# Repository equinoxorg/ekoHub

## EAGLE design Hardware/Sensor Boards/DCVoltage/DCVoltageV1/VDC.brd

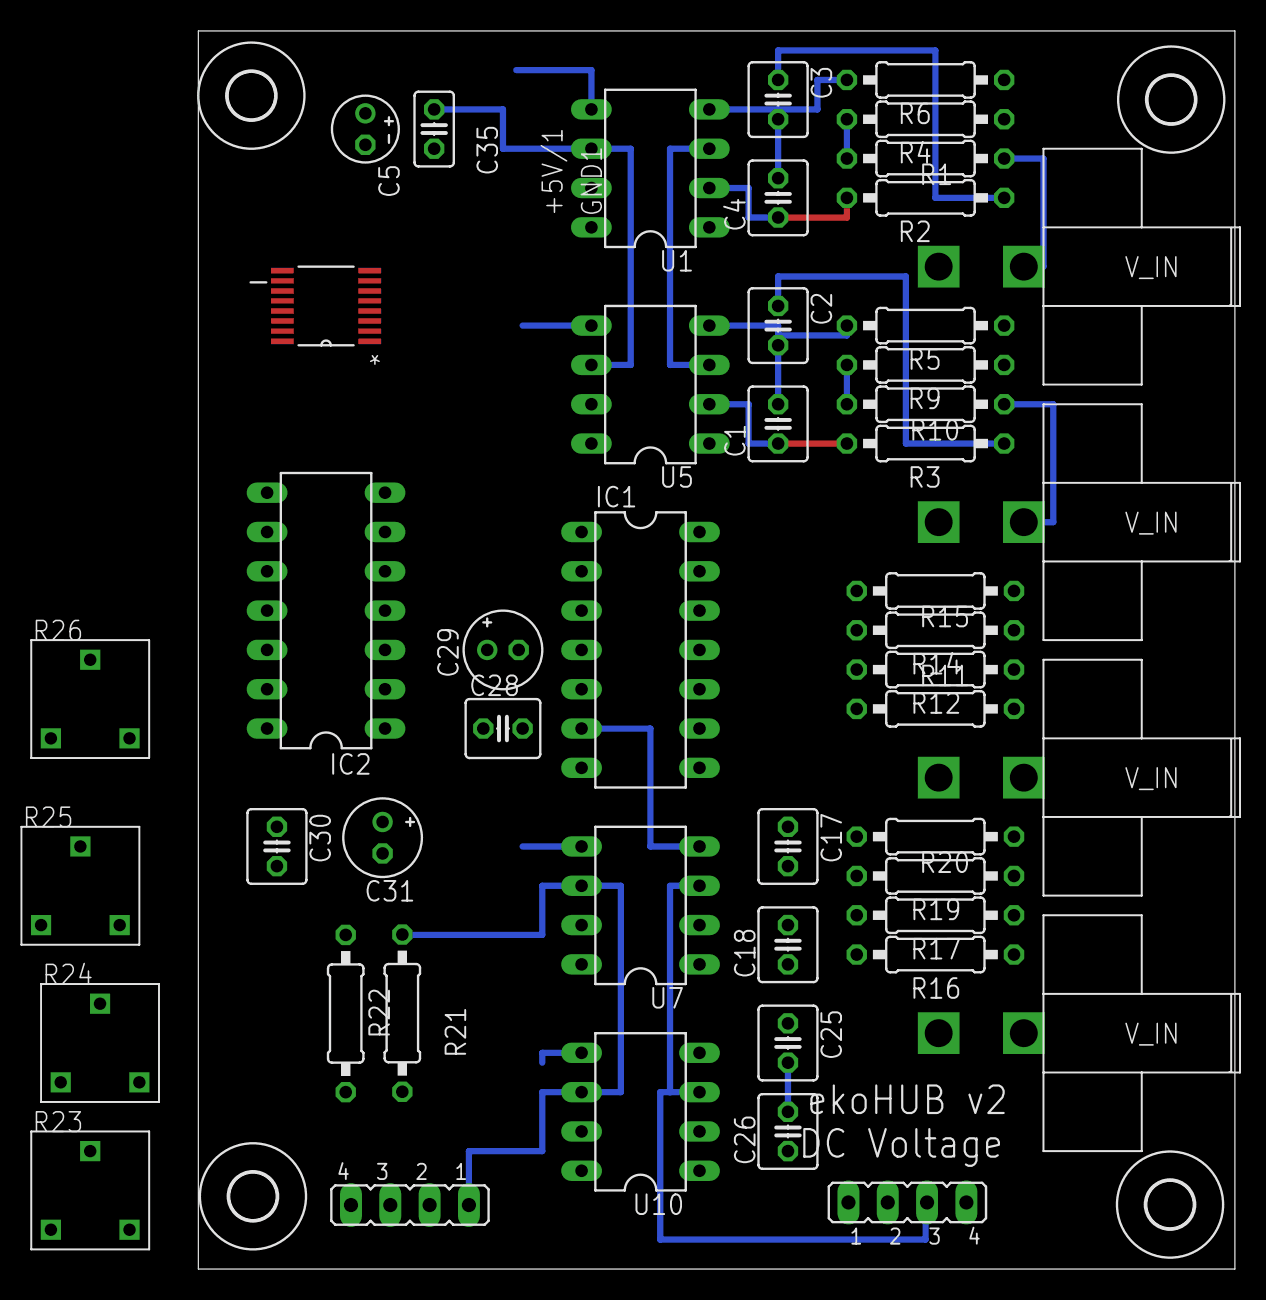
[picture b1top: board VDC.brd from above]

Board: 2 copper layers, 67.0 x 80.0 mm, 53 parts (0 on the bottom side), 34 nets.

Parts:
C1, C2, C3, C4, C17, C18, C25, C26, C28, C30: C025-040X050
C5: E2-4
C29, C31: E2-5
C35: C025-025X050
IC1, IC2: MCP604P; DIL14
JP1, JP3: JP4
R1, R2, R3, R4, R5, R6, R9, R10, R11, R12, R14, R15, R16, R17, R19, R20, R21, R22: 0207/10
R23, R24, R25, R26: IRG2014TRIM
U1, U5, U7, U10: IL300; DIL08
U13: AD7993BRUZ-0; SOP65P640X120-16N
U$1, U$2, U$3, U$4: 3,0
U$5, U$6, U$7, U$8: INPUT_VOLTAGE_CONNECTOR

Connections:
+5V/1: C28.1, C29.+, IC1.4, JP3.3, U1.3, U5.3, U7.3, U10.3
+5V/2: C5.+, C30.1, C31.+, C35.1, IC2.4, JP1.1, R21.1, R22.1, U1.6, U5.6, U7.6, U10.6, U13.5, U13.6
DC_OUT1: IC2.1, IC2.2, U13.7
DC_OUT2: IC2.6, IC2.7, U13.10
DC_OUT3: IC2.8, IC2.9, U13.8
DC_OUT4: IC2.13, IC2.14, U13.9
DC_SENSE1: R1.2, U$8.V+
DC_SENSE2: R10.2, U$7.V+
DC_SENSE3: R15.2, U$6.V+
DC_SENSE4: R20.2, U$5.V+
GND1: C28.2, C29.-, IC1.11, IC1.13, JP3.4, R4.1, R5.1, R6.1, R9.1, R12.1, R14.1, R17.1, R19.1, U1.1, U5.1, U7.1, U10.1, U$5.V-, U$6.V-, U$7.V-, U$8.V-
GND2: C5.-, C30.2, C31.-, C35.2, IC2.11, JP1.2, R23.P$1, R23.P$2, R24.P$1, R24.P$2, R25.P$1, R25.P$2, R26.P$1, R26.P$2, U13.1, U13.2, U13.3, U13.4, U13.11, U13.16
unnamed: C3.2, C4.2, R6.2, U1.4
unnamed: C1.2, C2.2, IC1.9, R5.2, U5.4
unnamed: IC2.12, R26.P$3, U1.5
unnamed: C4.1, R2.2, U1.2
unnamed: C3.1, IC1.14, R2.1
unnamed: C1.1, R3.2, U5.2
unnamed: C2.1, IC1.8, R3.1
unnamed: IC1.12, R1.1, R4.2
unnamed: IC2.10, R25.P$3, U5.5
unnamed: IC1.10, R9.2, R10.1
unnamed: C18.1, R11.2, U7.2
unnamed: C17.1, IC1.7, R11.1
unnamed: IC2.5, R24.P$3, U7.5
unnamed: IC1.5, R14.2, R15.1
unnamed: C25.2, C26.2, IC1.2, R17.2, U10.4
unnamed: C26.1, R16.2, U10.2
unnamed: C25.1, IC1.1, R16.1
unnamed: IC2.3, R23.P$3, U10.5
unnamed: IC1.3, R19.2, R20.1
unnamed: C17.2, C18.2, IC1.6, R12.2, U7.4
SCL: JP1.4, R22.2, U13.15
SDA: JP1.3, R21.2, U13.14

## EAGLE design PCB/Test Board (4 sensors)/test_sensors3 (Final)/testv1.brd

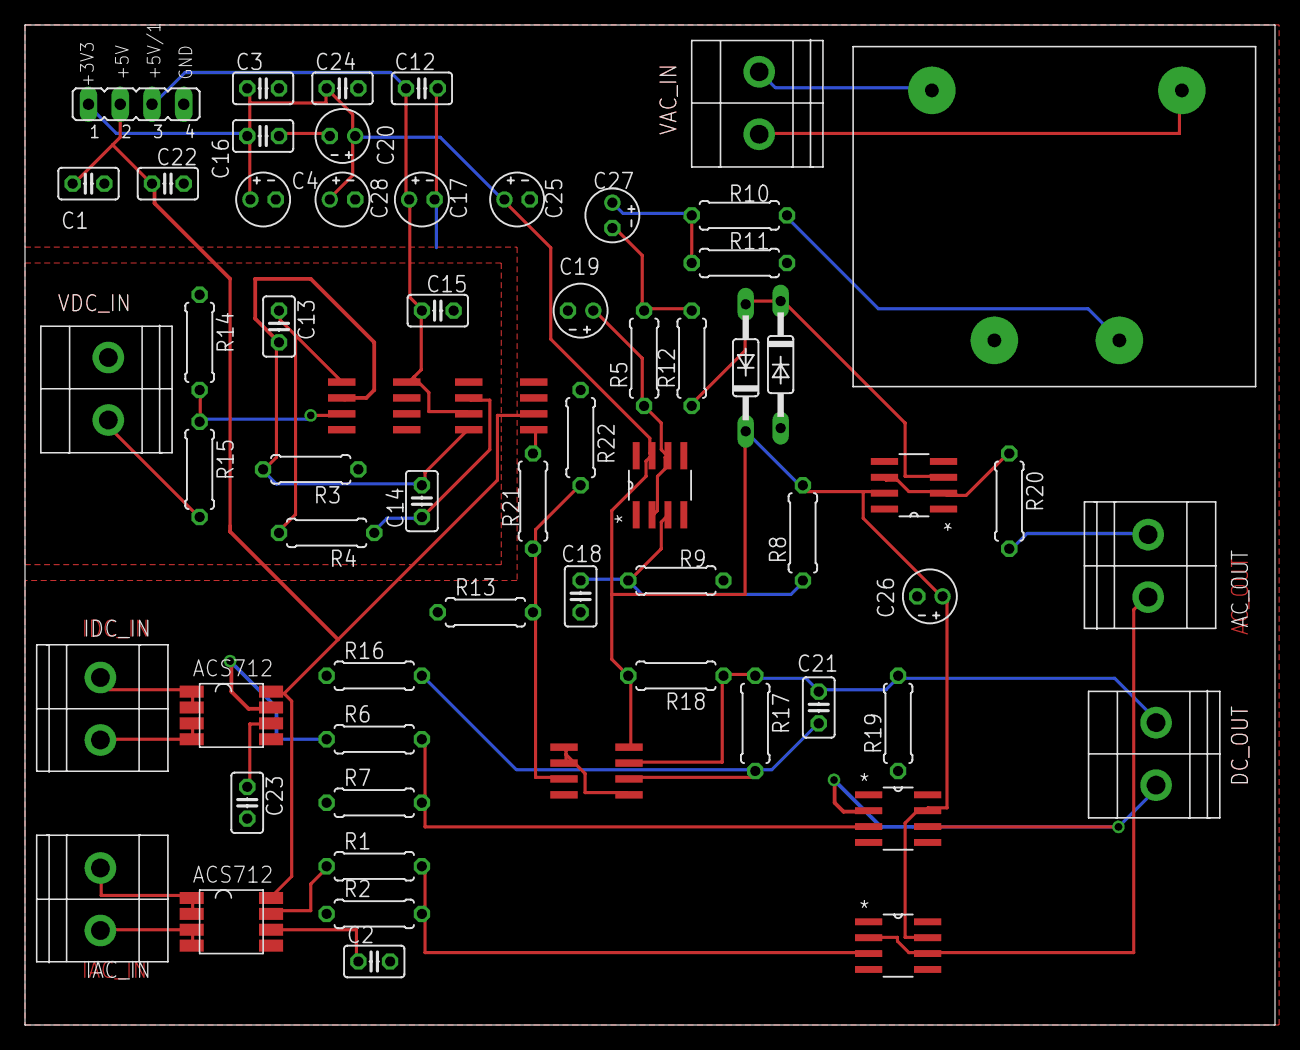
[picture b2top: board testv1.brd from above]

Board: 2 copper layers, 100.0 x 80.0 mm, 62 parts (0 on the bottom side), 38 nets.

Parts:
AC_OUT: CTB1500/2; CTB1500-2
C1, C2, C3, C12, C13, C14, C15, C16, C18, C21, C22, C23, C24: C025-025X050
C4, C17, C19, C20, C25, C26, C27, C28: E2-4
DC_OUT: CTB1500/2; CTB1500-2
IAC_IN: CTB1500/2; CTB1500-2
IC1, IC2: MCP602SN; SO08
IDC_IN: CTB1500/2; CTB1500-2
JP1: JP4
R1, R2, R3, R4, R5, R6, R7, R8, R9, R10, R11, R12, R13, R14, R15, R16, R17, R18, R19, R20, R21, R22: 0207/7
U2, U4, U5, U6: MCP601-E/SN; SOIC127P600X175-8N
U3: IL300; SO8
U$1, U$10: ACS712; SOIC8
U$6: 4408
U$7, U$8: SD103A; D035-10
VAC_IN: CTB1500/2; CTB1500-2
VDC_IN: CTB1500/2; CTB1500-2

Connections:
+3V3: C3.1, C4.+, C16.1, C20.+, C24.1, C25.+, C26.+, C28.+, IC2.8, JP1.1, R8.2, R18.2, U2.7, U4.7, U5.7, U6.7, U$7.C
+5V: C1.1, C22.1, JP1.2, U3.6, U$1.8, U$10.8
+5V/1: C12.1, C15.1, C17.+, IC1.8, JP1.3, U3.3
DC_SENSE: R15.2, VDC_IN.P$2
GND: C1.2, C2.2, C3.2, C4.-, C18.2, C19.-, C22.2, C23.2, C24.2, C25.-, C26.-, C28.-, IC2.4, JP1.4, R2.1, R7.1, R9.1, R11.1, R13.1, R16.1, R19.1, R22.1, U2.4, U4.4, U5.4, U6.4, U$1.5, U$6.PIN9, U$8.A, U$10.5
GND1: C12.2, C15.2, C17.-, IC1.4, IC1.5, IC1.6, R3.1, R14.1, U3.1, VDC_IN.P$1
GND2: C16.2, C20.-
IAC_OUT: AC_OUT.P$1, U2.2, U2.6
IDC_OUT: DC_OUT.P$2, U4.2, U4.6
unnamed: IAC_IN.P$2, U$1.1, U$1.2
unnamed: IAC_IN.P$1, U$1.3, U$1.4
unnamed: R1.1, U$1.7
unnamed: C2.1, U$1.6
unnamed: C13.2, C14.2, IC1.2, R3.2, U3.4
unnamed: R1.2, R2.2, U2.3
unnamed: C14.1, R4.1, U3.2
unnamed: IDC_IN.P$2, U$10.1, U$10.2
unnamed: C13.1, IC1.1, R4.2
unnamed: C18.1, R8.1, R9.2, U5.3
unnamed: C19.+, R5.1, U5.2, U5.6
unnamed: R12.1, U6.3, U$7.A, U$8.C
unnamed: R20.1, U6.2, U6.6
unnamed: IC2.3, R13.2, R21.2, R22.2
unnamed: R21.1, U3.5
unnamed: C27.+, R10.2, R11.2
unnamed: R10.1, U$6.PIN7
unnamed: IC2.1, IC2.2, IC2.5
unnamed: C27.-, R5.2, R12.2
unnamed: C21.1, IC2.6, R16.2, R17.2
unnamed: IC1.3, R14.2, R15.1
unnamed: IDC_IN.P$1, U$10.3, U$10.4
unnamed: R6.1, U$10.7
unnamed: C23.1, U$10.6
unnamed: R6.2, R7.2, U4.3
VAC_OUT: AC_OUT.P$2, R20.2
VDC_OUT: C21.2, DC_OUT.P$1, IC2.7, R17.1, R18.1, R19.2
V_IN1: U$6.PIN5, VAC_IN.P$2
V_IN2: U$6.PIN1, VAC_IN.P$1

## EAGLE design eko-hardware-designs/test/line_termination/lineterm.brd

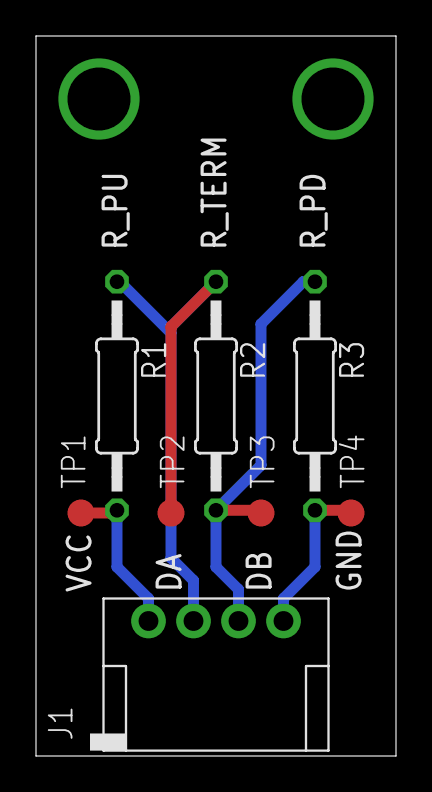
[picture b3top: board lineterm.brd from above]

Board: 2 copper layers, 20.0 x 40.0 mm, 8 parts (0 on the bottom side), 4 nets.

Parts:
J1: MB_CONN; PTSM0,5/4-HH-2,5-THR
R1: R_PU; 0207/12
R2: R_TERM; 0207/12
R3: R_PD; 0207/12
TP1, TP2, TP3, TP4: PTR1TP15R; TP15R

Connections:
GND: J1.4, R3.1, TP4.TP
unnamed: J1.3, R2.1, R3.2, TP3.TP
unnamed: J1.2, R1.1, R2.2, TP2.TP
VCC: J1.1, R1.2, TP1.TP

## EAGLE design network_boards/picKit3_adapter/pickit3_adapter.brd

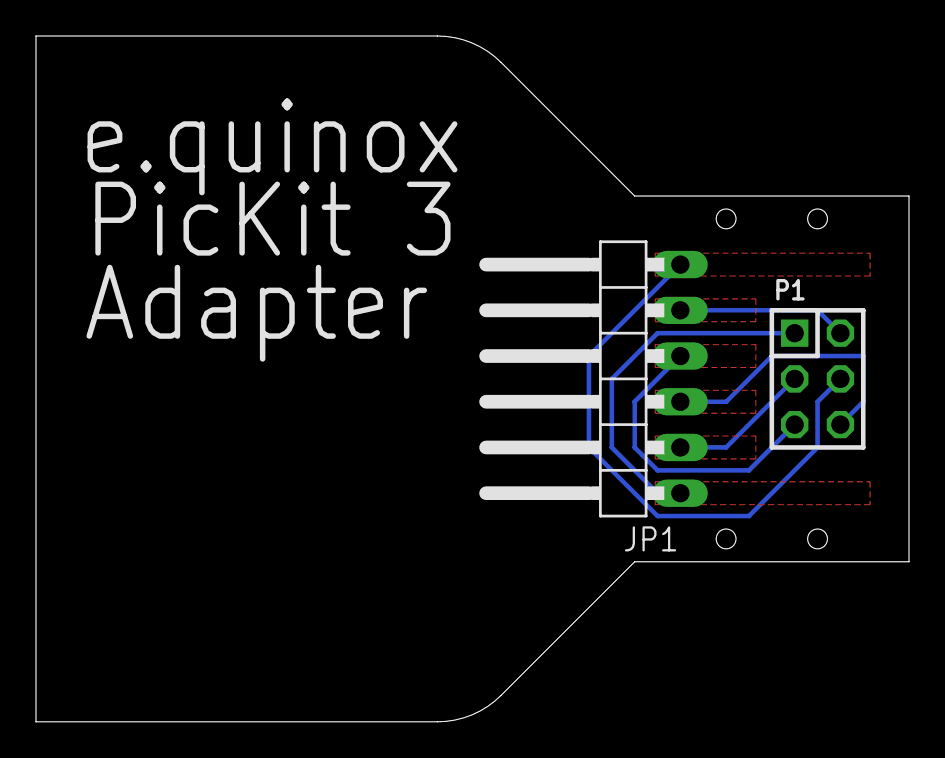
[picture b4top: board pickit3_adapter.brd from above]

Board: 2 copper layers, 48.5 x 38.1 mm, 3 parts (1 on the bottom side), 6 nets.

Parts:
JP1: 1X06/90
P1: ICSP; DIL-100-2X03
U$1: EQNXLOGO

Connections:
0V: JP1.3, P1.6
!MCLR!: JP1.1, P1.1
+3V3: JP1.2, P1.3
PGC: JP1.5, P1.2
PGD: JP1.4, P1.5
PGM: JP1.6, P1.4

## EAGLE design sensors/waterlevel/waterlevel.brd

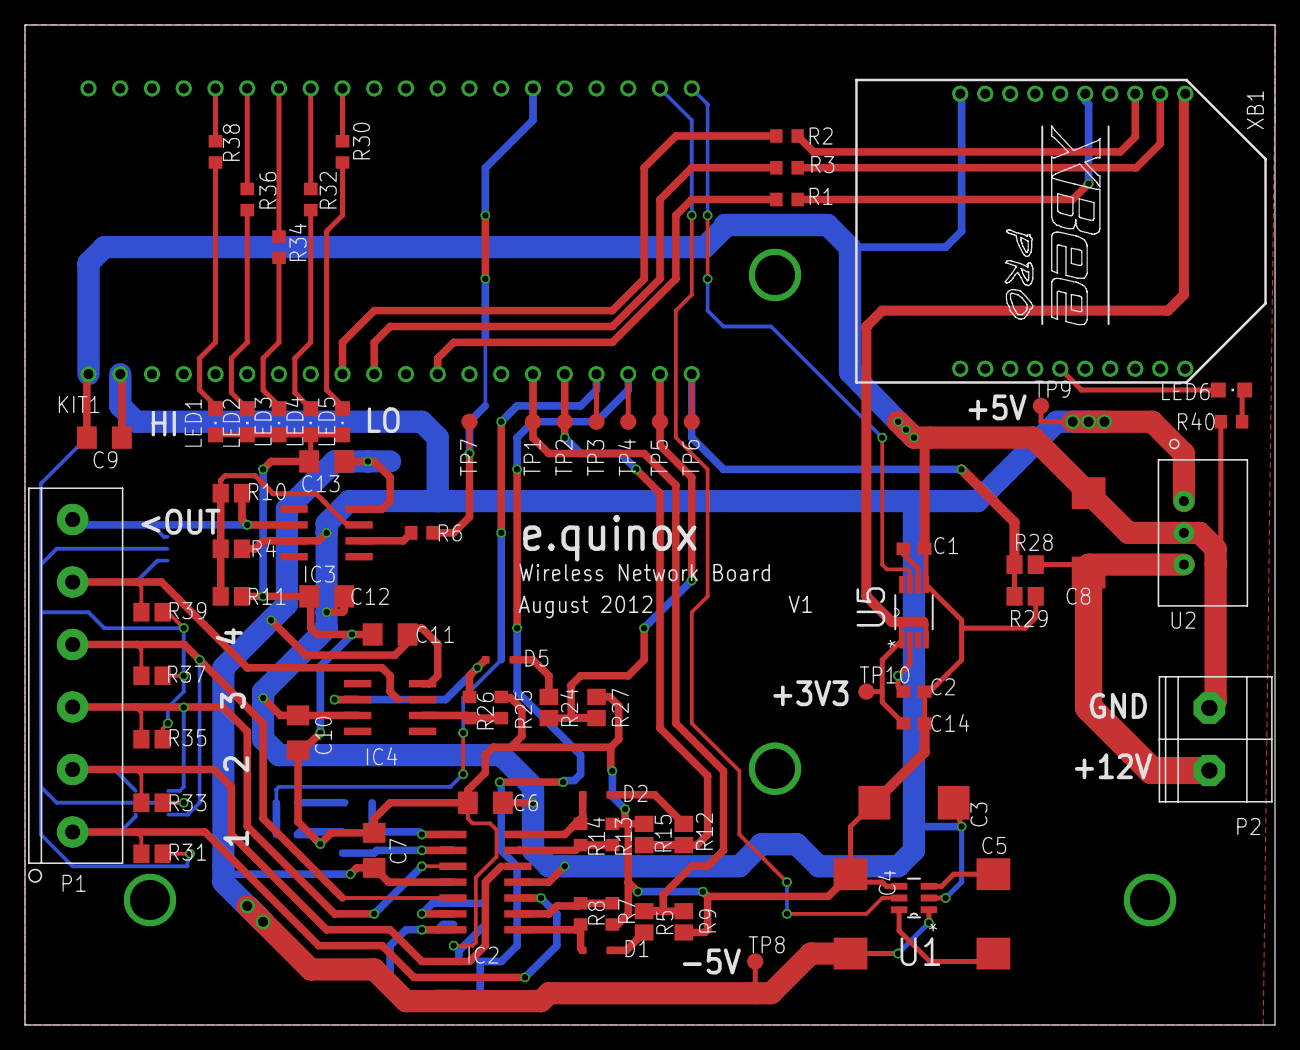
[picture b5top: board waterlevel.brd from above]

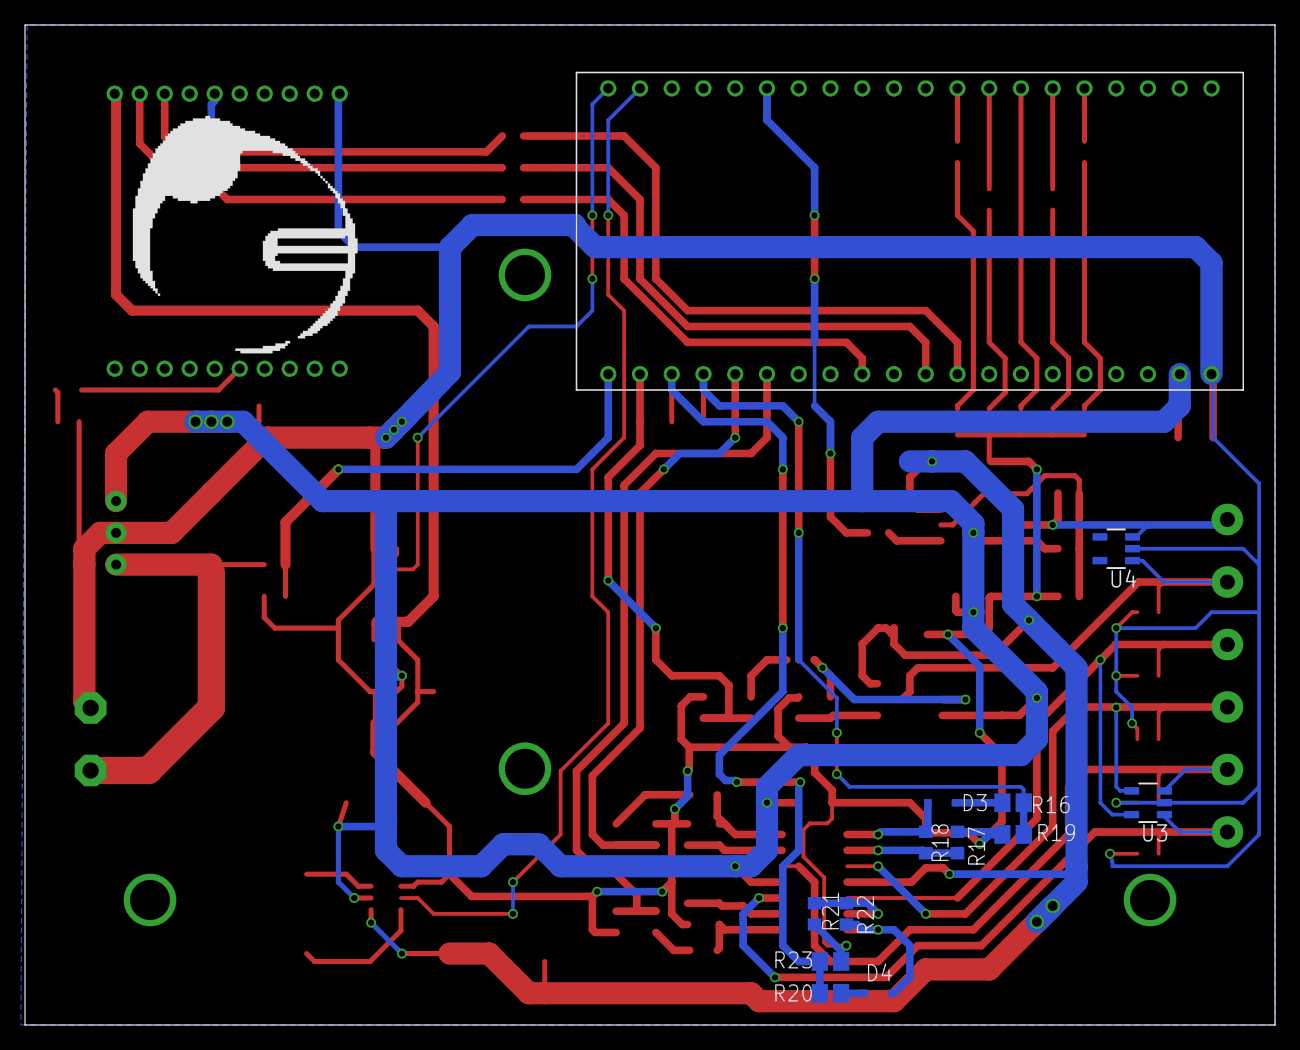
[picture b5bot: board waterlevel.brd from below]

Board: 2 copper layers, 100.0 x 80.0 mm, 88 parts (13 on the bottom side), 58 nets.

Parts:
C1: 33nF; C0603
C2, C14: 2.2u; C0603
C3, C4, C5: 10uF; D/7343-31R
C6, C7, C10, C11, C12, C13: 100n; C1206
C8: 47uF; D/7343-31R
C9: 1uF; C1206
D1, D2, D3, D4, D5: SOD323-R
IC2: MCP604SL; SO14
IC3, IC4: MCP601SN; SO08
KIT1: MBED_NXP_LPC1768; MBED-KIT
LED1: RED; CHIPLED_0805
LED2: AMBER; CHIPLED_0805
LED3, LED4, LED5: GREEN; CHIPLED_0805
LED6: CHIPLED_0805
P1: CAMDEN-CTB5000/6; CAMDEN-CTB5000
P2: CTB1500/2; CTB1500-2
R1, R2, R3: 33; R0603
R4, R5, R9, R11, R12, R15, R16, R19, R20, R23, R24, R27, R29: 1k; R0805
R6, R8, R14, R18, R22, R26: 0; R0603
R7, R13, R17, R21, R25: DNP; R0603
R10: 100k; R0805
R28: 3k; R0805
R30, R32, R34, R36, R38, R40: 200; R0603
R31, R33, R35, R37, R39: 1M; R0805
TP1, TP2, TP3, TP4, TP5, TP6, TP7, TP8, TP9, TP10: TPTP13R; TP13R
U1: NCP1729SN35T1G; SOP95P275X110-6N
U2: SR05S05; XP-SR-SERIES
U3, U4: VISHAY-VCUT05A4; SOT23-5
U5: LP3981IMM-3.3; SOP65P490X110-8N
U$2: EQNXLOGO
XB1: XBEE-PRO

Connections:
!XBEE_RESET!: KIT1.P$12, R1.1
+3V3: C14.1, TP10.TP, U5.1, U5.4, XB1.1
+5V: C2.1, C3.+, C6.1, C9.1, C10.1, C12.1, IC2.4, IC3.7, IC4.7, KIT1.VIN, R4.2, TP9.TP, U1.2, U2.1, U5.2
+12V: C8.+, P2.P$1, R28.2, U2.3
-5V: C4.+, C7.1, C11.1, C13.1, IC2.11, IC3.4, IC4.4, TP8.TP, U1.1
BAT_LVL: KIT1.P$20, R28.1, R29.2, TP6.TP
GND: C1.2, C2.2, C3.-, C4.-, C6.2, C7.2, C8.-, C9.2, C10.2, C11.2, C12.2, C13.2, C14.2, KIT1.GND, LED1.C, LED2.C, LED3.C, LED4.C, LED5.C, P2.P$2, R7.1, R9.1, R11.1, R13.1, R15.1, R17.1, R19.1, R21.1, R23.1, R25.1, R27.1, R29.1, R31.1, R33.1, R35.1, R37.1, R39.1, R40.1, U1.4, U2.2, U3.2, U4.2, U5.5, XB1.10
LED1: KIT1.RD-, R38.2
LED2: KIT1.RD+, R36.2
LED3: KIT1.TD-, R34.2
LED4: KIT1.TD+, R32.2
LED5: KIT1.D-, R30.2
LVL1: KIT1.P$15, R5.1, R9.2, TP1.TP
LVL2: KIT1.P$16, R12.1, R15.2, TP2.TP
LVL3: KIT1.P$17, R16.1, R19.2, TP3.TP
LVL4: KIT1.P$18, R20.1, R23.2, TP4.TP
LVL5: KIT1.P$19, R24.1, R27.2, TP5.TP
MBED_RX: KIT1.P$10, R3.1
MBED_TX: KIT1.P$9, R2.1
N5V_ON: KIT1.P$22, U1.5
unnamed: IC3.2, R6.2
unnamed: D2.A, IC2.7, R14.2
unnamed: D3.A, IC2.8, R18.2
unnamed: D4.A, IC2.14, R22.2
unnamed: D5.A, IC4.6, R26.2
unnamed: IC4.2, R25.2, R26.1
unnamed: IC2.13, R21.2, R22.1
unnamed: IC2.9, R17.2, R18.1
unnamed: IC2.6, R13.2, R14.1
unnamed: IC2.2, R7.2, R8.1
unnamed: C5.+, U1.6
unnamed: D2.C, R12.2
unnamed: C5.-, U1.3
unnamed: D1.C, R5.2
unnamed: D1.A, IC2.1, R8.2
unnamed: D3.C, R16.2
unnamed: LED6.A, XB1.15
unnamed: D4.C, R20.2
unnamed: R1.2, XB1.5
unnamed: D5.C, R24.2
unnamed: R2.2, XB1.3
unnamed: R3.2, XB1.2
unnamed: IC3.3, R4.1, R10.2, R11.2
unnamed: LED6.C, R40.2
unnamed: LED5.A, R30.1
unnamed: LED4.A, R32.1
unnamed: LED3.A, R34.1
unnamed: C1.1, U5.6
unnamed: LED2.A, R36.1
unnamed: LED1.A, R38.1
SENSOR_IN_1: IC2.3, P1.1, R31.2, U3.1
SENSOR_IN_2: IC2.5, P1.2, R33.2, U3.3
SENSOR_IN_3: IC2.10, P1.3, R35.2, U3.4
SENSOR_IN_4: IC2.12, P1.4, R37.2, U3.5
SENSOR_IN_5: IC4.3, P1.5, R39.2, U4.1
SQR_IN: KIT1.P$26, R6.1, TP7.TP
SQR_OUT_AC: IC3.6, P1.6, R10.1, U4.3
XBEE_PWR_ON: KIT1.P$21, U5.7

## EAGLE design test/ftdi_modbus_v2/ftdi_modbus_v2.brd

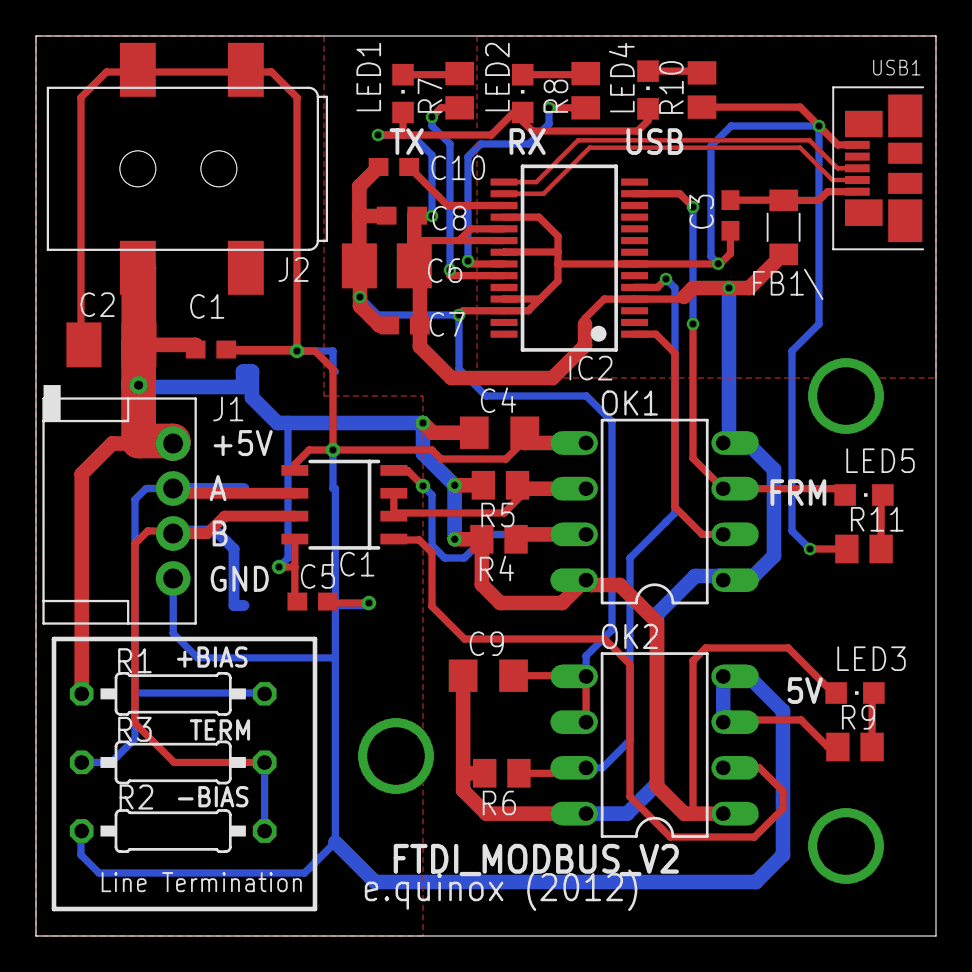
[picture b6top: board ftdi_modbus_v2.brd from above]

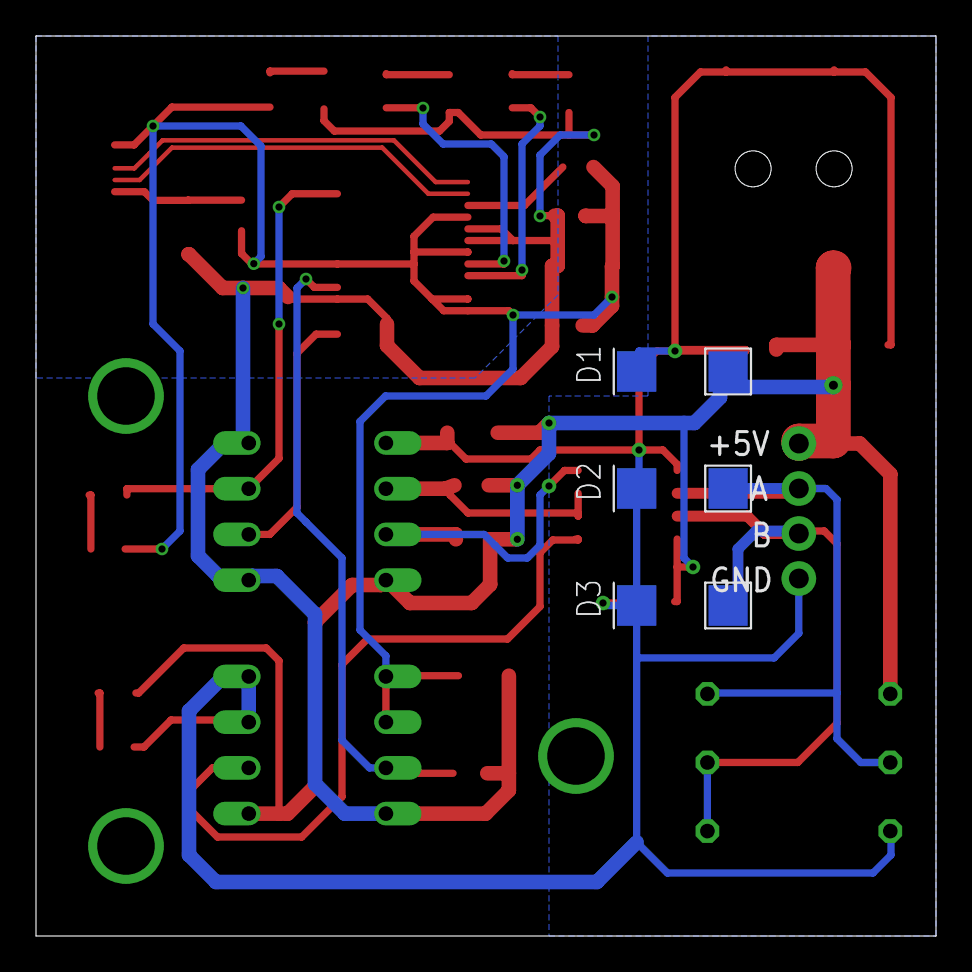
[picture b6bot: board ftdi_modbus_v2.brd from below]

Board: 2 copper layers, 50.0 x 50.0 mm, 37 parts (3 on the bottom side), 23 nets.

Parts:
C1, C5, C7, C8, C10: 100nF; C0603
C2, C6: 4.7uF; B/3528-21R
C3: 10nF; C0603
C4, C9: 100nF; C1206
D1, D2, D3: SMBJ7.0CA; DO214AA
FB1\: 500mA; L3216C
IC1: SP483E; D_R-PDSO-G8
IC2: FT232RL; SSOP28
J1: MB_CONN; PTSM0,5/4-HH-2,5-THR
J2: CLIFF_DCJACK2.1-2.5MM; FC6814XS
LED1: GREEN; CHIPLED_0805
LED2, LED3, LED4, LED5: AMBER; CHIPLED_0805
OK1, OK2: HCPL2630; DIL08
R1, R2, R3: 0207/10
R4, R5, R6: 4.7k; M0805
R7, R8, R9, R10, R11: 270; M0805
USB1: MOLEX47346-0001; 47346-0001

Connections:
+3V3: C10.1, IC2.17
+5V/1: C6.+, C7.1, C8.1, C9.1, FB1\.1, IC2.4, IC2.19, IC2.20, LED1.A, LED2.A, LED4.A, OK1.1, OK1.4, OK2.8, R6.2
+5V/2: C1.1, C2.+, C4.1, C5.1, D1.P$1, IC1.8, J1.1, J2.3, LED3.A, OK1.8, OK2.1, R1.2, R4.2, R5.2
FTDI_RXD: IC2.5, OK2.7, R6.1
FTDI_TXD: IC2.1, OK1.2
FTDI_TXEN: IC2.13, LED5.A, OK1.3
GND1: C3.2, C6.-, C7.2, C8.2, C9.2, C10.2, IC2.7, IC2.18, IC2.21, IC2.25, IC2.26, OK2.5, OK2.6, R10.1, R11.1, USB1.5
GND2: C1.2, C2.-, C4.2, C5.2, D1.P$2, D2.P$2, D3.P$2, IC1.5, J1.4, J2.1A, J2.1B, OK1.5, OK2.3, OK2.4, R2.1, R9.1
ISO_RXD: IC1.1, OK2.2
ISO_TXD: IC1.4, OK1.7, R4.1
ISO_TXEN: IC1.2, IC1.3, OK1.6, R5.1
unnamed: C3.1, FB1\.2, USB1.1
unnamed: LED1.C, R7.2
unnamed: LED2.C, R8.2
unnamed: LED3.C, R9.2
unnamed: LED4.C, R10.2
unnamed: LED5.C, R11.2
RS485_N: D3.P$1, IC1.7, J1.3, R2.2, R3.1
RS485_P: D2.P$1, IC1.6, J1.2, R1.1, R3.2
RX_LED: IC2.22, R8.1
TX_LED: IC2.23, R7.1
USB_N: IC2.16, USB1.2
USB_P: IC2.15, USB1.3
